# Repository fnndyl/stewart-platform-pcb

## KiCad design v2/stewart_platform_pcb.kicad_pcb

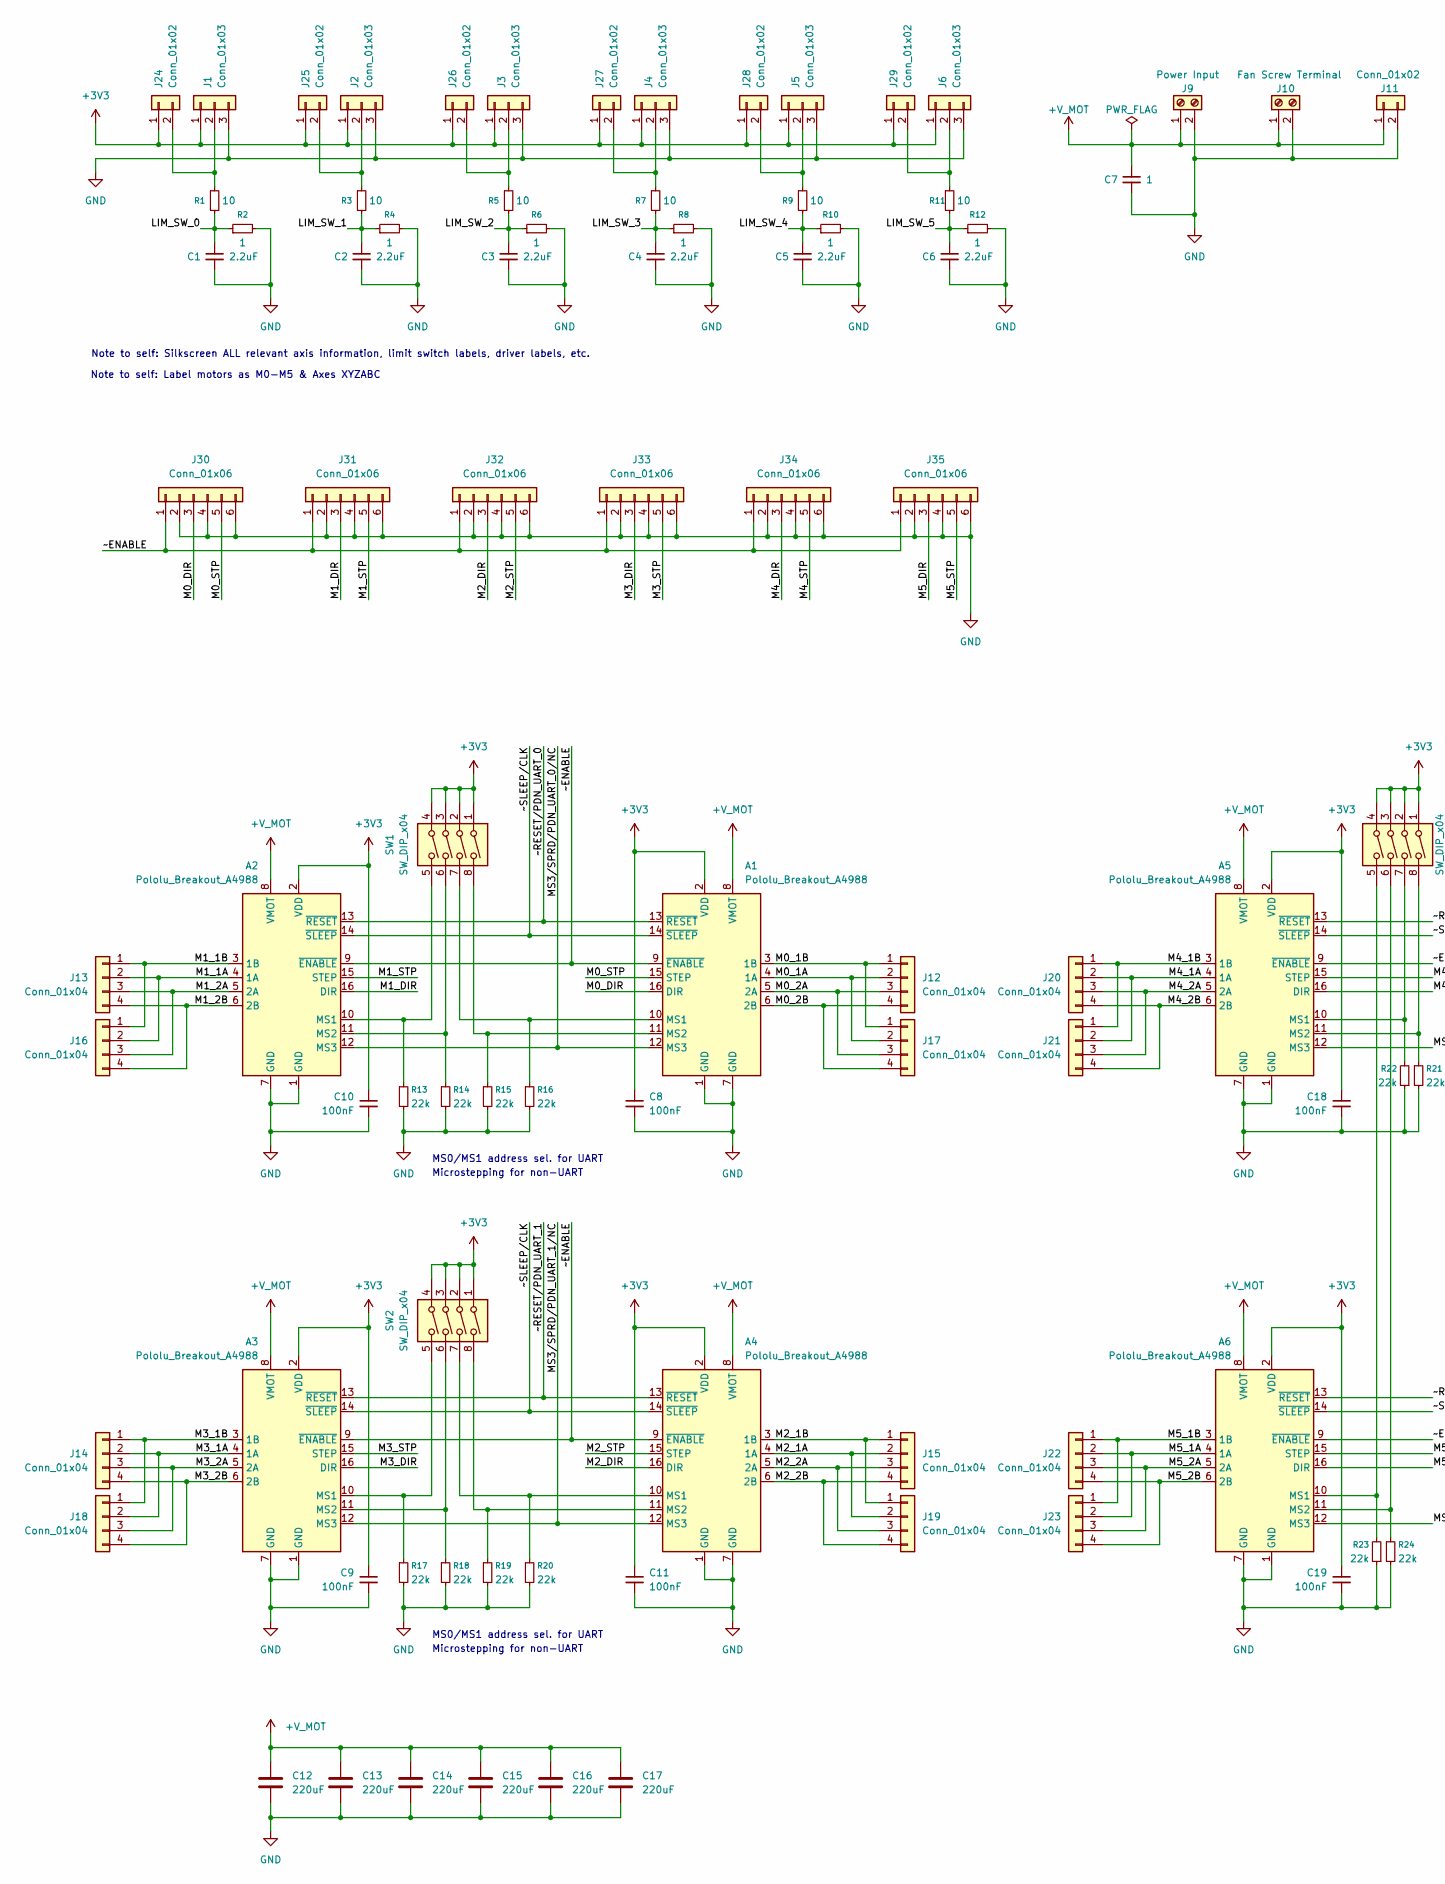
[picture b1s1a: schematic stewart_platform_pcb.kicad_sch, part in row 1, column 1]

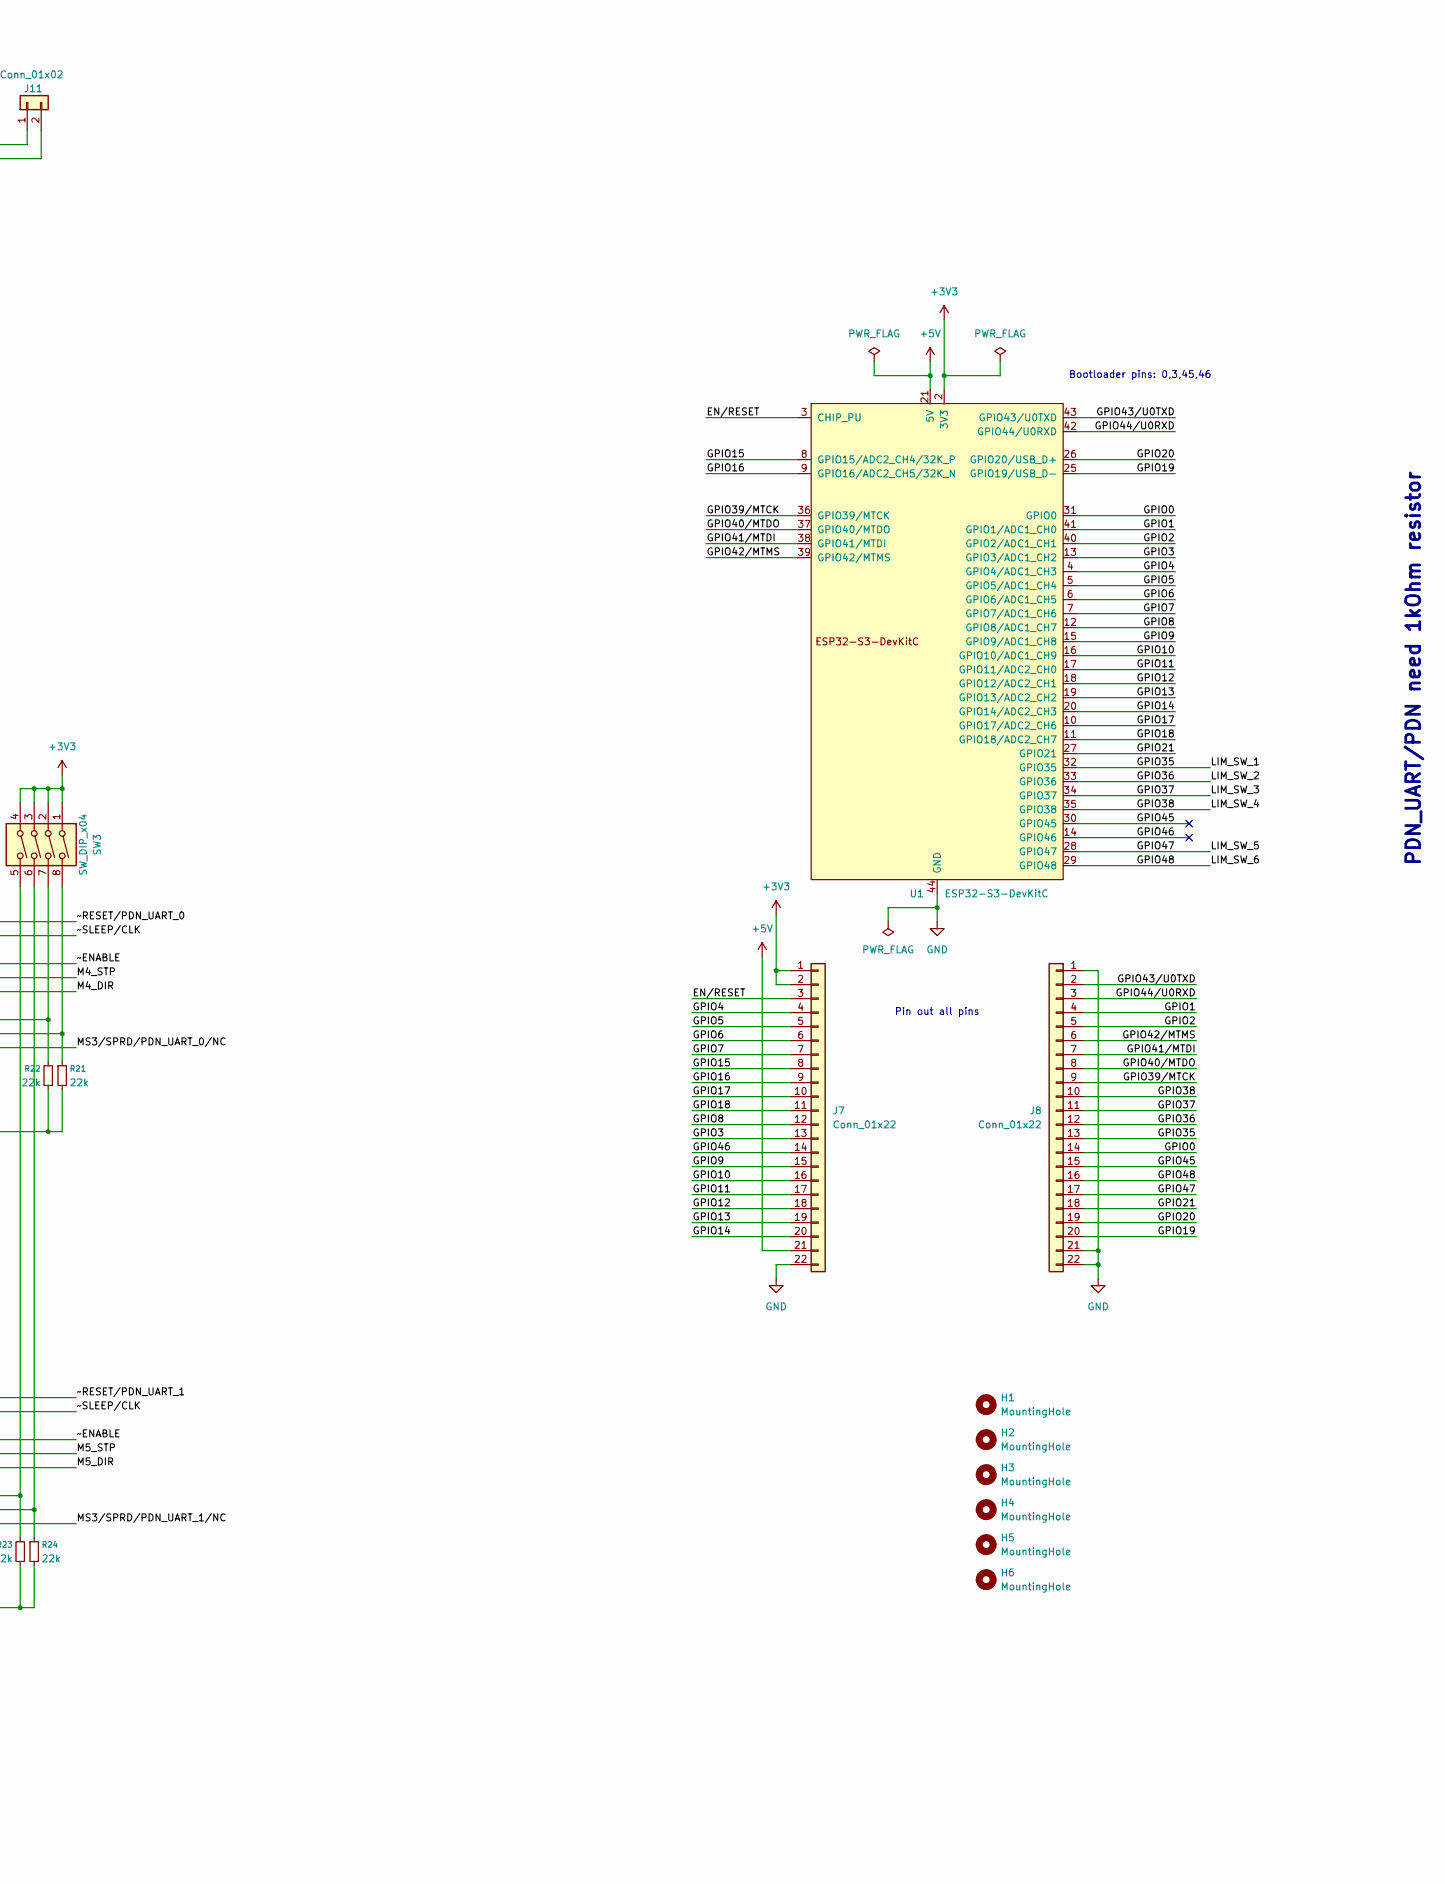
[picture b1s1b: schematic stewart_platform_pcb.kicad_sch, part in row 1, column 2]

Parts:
A1, A2, A3, A4, A5, A6: Pololu_Breakout_A4988; Pololu_Breakout-16_15.2x20.3mm
C1, C2, C3, C4, C5, C6: 2.2uF; C_Radial_D6.3mm_H5.0mm_P2.50mm
C7: 1
C8, C9, C10, C11, C18, C19: 100nF; C_Disc_D4.3mm_W1.9mm_P5.00mm
C12, C13, C14, C15, C16, C17: 220uF; C_Radial_D10.0mm_H12.5mm_P5.00mm
H1, H2, H3, H4, H5, H6: MountingHole; MountingHole_3.2mm_M3
J1, J2, J3, J4, J5, J6: Conn_01x03; JST_XH_B3B-XH-A_1x03_P2.50mm_Vertical
J7, J8: Conn_01x22; PinHeader_1x22_P2.54mm_Vertical
J9: Power Input; TerminalBlock_Phoenix_MKDS-1,5-2_1x02_P5.00mm_Horizontal
J10: Fan Screw Terminal; TerminalBlock_Phoenix_MKDS-1,5-2_1x02_P5.00mm_Horizontal
J11, J24, J25, J26, J27, J28, J29: Conn_01x02; JST_XH_B2B-XH-A_1x02_P2.50mm_Vertical
J12, J13, J14, J15, J16, J17, J18, J19, J20, J21, J22, J23: Conn_01x04; JST_XH_B4B-XH-A_1x04_P2.50mm_Vertical
J30, J31, J32, J33, J34, J35: Conn_01x06; JST_XH_B6B-XH-A_1x06_P2.50mm_Vertical
R1, R3, R5, R7, R9, R11: 10; R_Axial_DIN0207_L6.3mm_D2.5mm_P7.62mm_Horizontal
R2, R4, R6, R8, R10, R12: 1; R_Axial_DIN0207_L6.3mm_D2.5mm_P7.62mm_Horizontal
R13, R14, R15, R16, R17, R18, R19, R20, R21, R22, R23, R24: 22k; R_Axial_DIN0207_L6.3mm_D2.5mm_P7.62mm_Horizontal
SW1, SW2, SW3: SW_DIP_x04; SW_DIP_SPSTx04_Slide_9.78x12.34mm_W7.62mm_P2.54mm
U1: ESP32-S3-DevKitC

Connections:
+3V3: A1.2 (VDD), A2.2 (VDD), A3.2 (VDD), A4.2 (VDD), A5.2 (VDD), A6.2 (VDD), C8.1, C9.1, C10.1, C11.1, C18.1, C19.1, J1.1, J2.1, J3.1, J4.1, J5.1, J6.1, J7.1, J7.2, J24.1, J25.1, J26.1, J27.1, J28.1, J29.1, SW1.1, SW1.2, SW1.3, SW1.4, SW2.1, SW2.2, SW2.3, SW2.4, SW3.1, SW3.2, SW3.3, SW3.4, U1.1 (3V3), U1.2 (3V3)
+5V: J7.21, U1.21 (5V)
+V_MOT: A1.8 (VMOT), A2.8 (VMOT), A3.8 (VMOT), A4.8 (VMOT), A5.8 (VMOT), A6.8 (VMOT), C7.1, C12.1, C13.1, C14.1, C15.1, C16.1, C17.1, J9.1, J10.1, J11.1
/EN/RESET: J7.3, U1.3 (CHIP_PU)
/GPIO0: J8.14, U1.31 (GPIO0)
/GPIO1: J8.4, U1.41 (GPIO1/ADC1_CH0)
/GPIO2: J8.5, U1.40 (GPIO2/ADC1_CH1)
/GPIO3: J7.13, U1.13 (GPIO3/ADC1_CH2)
/GPIO4: J7.4, U1.4 (GPIO4/ADC1_CH3)
/GPIO5: J7.5, U1.5 (GPIO5/ADC1_CH4)
/GPIO6: J7.6, U1.6 (GPIO6/ADC1_CH5)
/GPIO7: J7.7, U1.7 (GPIO7/ADC1_CH6)
/GPIO8: J7.12, U1.12 (GPIO8/ADC1_CH7)
/GPIO9: J7.15, U1.15 (GPIO9/ADC1_CH8)
/GPIO10: J7.16, U1.16 (GPIO10/ADC1_CH9)
/GPIO11: J7.17, U1.17 (GPIO11/ADC2_CH0)
/GPIO12: J7.18, U1.18 (GPIO12/ADC2_CH1)
/GPIO13: J7.19, U1.19 (GPIO13/ADC2_CH2)
/GPIO14: J7.20, U1.20 (GPIO14/ADC2_CH3)
/GPIO15: J7.8, U1.8 (GPIO15/ADC2_CH4/32K_P)
/GPIO16: J7.9, U1.9 (GPIO16/ADC2_CH5/32K_N)
/GPIO17: J7.10, U1.10 (GPIO17/ADC2_CH6)
/GPIO18: J7.11, U1.11 (GPIO18/ADC2_CH7)
/GPIO19: J8.20, U1.25 (GPIO19/USB_D-)
/GPIO20: J8.19, U1.26 (GPIO20/USB_D+)
/GPIO21: J8.18, U1.27 (GPIO21)
/GPIO35: C2.1, J8.13, R3.2, R4.1, U1.32 (GPIO35)
/GPIO36: C3.1, J8.12, R5.2, R6.1, U1.33 (GPIO36)
/GPIO37: C4.1, J8.11, R7.2, R8.1, U1.34 (GPIO37)
/GPIO38: C5.1, J8.10, R9.2, R10.1, U1.35 (GPIO38)
/GPIO39/MTCK: J8.9, U1.36 (GPIO39/MTCK)
/GPIO40/MTDO: J8.8, U1.37 (GPIO40/MTDO)
/GPIO41/MTDI: J8.7, U1.38 (GPIO41/MTDI)
/GPIO42/MTMS: J8.6, U1.39 (GPIO42/MTMS)
/GPIO43/U0TXD: J8.2, U1.43 (GPIO43/U0TXD)
/GPIO44/U0RXD: J8.3, U1.42 (GPIO44/U0RXD)
/GPIO45: J8.15, U1.30 (GPIO45)
/GPIO46: J7.14, U1.14 (GPIO46)
/GPIO47: C6.1, J8.17, R11.2, R12.1, U1.28 (GPIO47)
/GPIO48: J8.16, U1.29 (GPIO48)
/LIM_SW_0: C1.1, R1.2, R2.1
/M0_1A: A1.4 (1A), J12.2, J17.2
/M0_1B: A1.3 (1B), J12.1, J17.1
/M0_2A: A1.5 (2A), J12.3, J17.3
/M0_2B: A1.6 (2B), J12.4, J17.4
/M0_DIR: A1.16 (DIR), J30.3
/M0_STP: A1.15 (STEP), J30.5
/M1_1A: A2.4 (1A), J13.2, J16.2
/M1_1B: A2.3 (1B), J13.1, J16.1
/M1_2A: A2.5 (2A), J13.3, J16.3
/M1_2B: A2.6 (2B), J13.4, J16.4
/M1_DIR: A2.16 (DIR), J31.3
/M1_STP: A2.15 (STEP), J31.5
/M2_1A: A4.4 (1A), J15.2, J19.2
/M2_1B: A4.3 (1B), J15.1, J19.1
/M2_2A: A4.5 (2A), J15.3, J19.3
/M2_2B: A4.6 (2B), J15.4, J19.4
/M2_DIR: A4.16 (DIR), J32.3
/M2_STP: A4.15 (STEP), J32.5
/M3_1A: A3.4 (1A), J14.2, J18.2
/M3_1B: A3.3 (1B), J14.1, J18.1
/M3_2A: A3.5 (2A), J14.3, J18.3
/M3_2B: A3.6 (2B), J14.4, J18.4
/M3_DIR: A3.16 (DIR), J33.3
/M3_STP: A3.15 (STEP), J33.5
/M4_1A: A5.4 (1A), J20.2, J21.2
/M4_1B: A5.3 (1B), J20.1, J21.1
/M4_2A: A5.5 (2A), J20.3, J21.3
/M4_2B: A5.6 (2B), J20.4, J21.4
/M4_DIR: A5.16 (DIR), J34.3
/M4_STP: A5.15 (STEP), J34.5
/M5_1A: A6.4 (1A), J22.2, J23.2
/M5_1B: A6.3 (1B), J22.1, J23.1
/M5_2A: A6.5 (2A), J22.3, J23.3
/M5_2B: A6.6 (2B), J22.4, J23.4
/M5_DIR: A6.16 (DIR), J35.3
/M5_STP: A6.15 (STEP), J35.5
/MS3/SPRD/PDN_UART_0/NC: A1.12 (MS3), A2.12 (MS3), A5.12 (MS3)
/MS3/SPRD/PDN_UART_1/NC: A3.12 (MS3), A4.12 (MS3), A6.12 (MS3)
/~ENABLE: A1.9 (~ENABLE), A2.9 (~ENABLE), A3.9 (~ENABLE), A4.9 (~ENABLE), A5.9 (~ENABLE), A6.9 (~ENABLE), J30.1, J31.1, J32.1, J33.1, J34.1, J35.1
/~RESET/PDN_UART_0: A1.13 (~RESET), A2.13 (~RESET), A5.13 (~RESET)
/~RESET/PDN_UART_1: A3.13 (~RESET), A4.13 (~RESET), A6.13 (~RESET)
/~SLEEP/CLK: A1.14 (~SLEEP), A2.14 (~SLEEP), A3.14 (~SLEEP), A4.14 (~SLEEP), A5.14 (~SLEEP), A6.14 (~SLEEP)
GND: A1.1 (GND), A1.7 (GND), A2.1 (GND), A2.7 (GND), A3.1 (GND), A3.7 (GND), A4.1 (GND), A4.7 (GND), A5.1 (GND), A5.7 (GND), A6.1 (GND), A6.7 (GND), C1.2, C2.2, C3.2, C4.2, C5.2, C6.2, C7.2, C8.2, C9.2, C10.2, C11.2, C12.2, C13.2, C14.2, C15.2, C16.2, C17.2, C18.2, C19.2, J1.3, J2.3, J3.3, J4.3, J5.3, J6.3, J7.22, J8.1, J8.21, J8.22, J9.2, J10.2, J11.2, J30.2, J30.4, J30.6, J31.2, J31.4, J31.6, J32.2, J32.4, J32.6, J33.2, J33.4, J33.6, J34.2, J34.4, J34.6, J35.2, J35.4, J35.6, R2.2, R4.2, R6.2, R8.2, R10.2, R12.2, R13.2, R14.2, R15.2, R16.2, R17.2, R18.2, R19.2, R20.2, R21.2, R22.1, R23.1, R24.2, U1.22 (GND), U1.23 (GND), U1.24 (GND), U1.44 (GND)
unnamed: A1.10 (MS1), R16.1, SW1.7
unnamed: A1.11 (MS2), R15.1, SW1.8
unnamed: A2.10 (MS1), R13.1, SW1.5
unnamed: A2.11 (MS2), R14.1, SW1.6
unnamed: A3.10 (MS1), R17.1, SW2.5
unnamed: A3.11 (MS2), R18.1, SW2.6
unnamed: A4.10 (MS1), R20.1, SW2.7
unnamed: A4.11 (MS2), R19.1, SW2.8
unnamed: A5.10 (MS1), R22.2, SW3.7
unnamed: A5.11 (MS2), R21.1, SW3.8
unnamed: A6.10 (MS1), R23.2, SW3.5
unnamed: A6.11 (MS2), R24.1, SW3.6
unnamed: J1.2, J24.2, R1.1
unnamed: J2.2, J25.2, R3.1
unnamed: J3.2, J26.2, R5.1
unnamed: J4.2, J27.2, R7.1
unnamed: J5.2, J28.2, R9.1
unnamed: J6.2, J29.2, R11.1

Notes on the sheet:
MS0/MS1 address sel. for UART
PDN_UART/PDN need 1kOhm resistor
Microstepping for non-UART
Pin out all pins
Note to self: Label motors as M0-M5 & Axes XYZABC
Note to self: Silkscreen ALL relevant axis information, limit switch labels, driver labels, etc.
Bootloader pins: 0,3,45,46

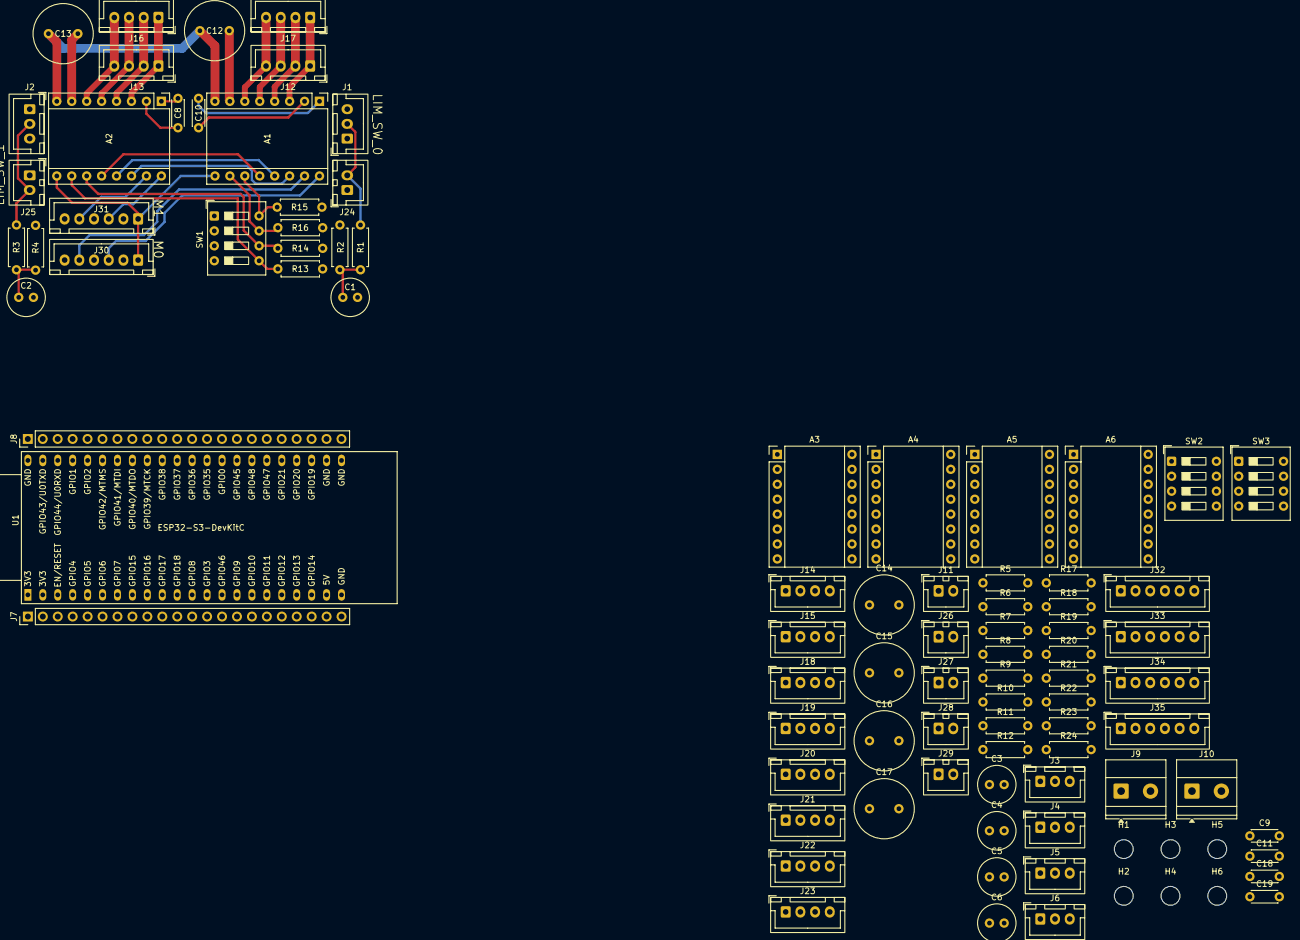
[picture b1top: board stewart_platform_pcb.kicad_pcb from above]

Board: 4 copper layers, 93 parts (0 on the bottom side), 102 nets.

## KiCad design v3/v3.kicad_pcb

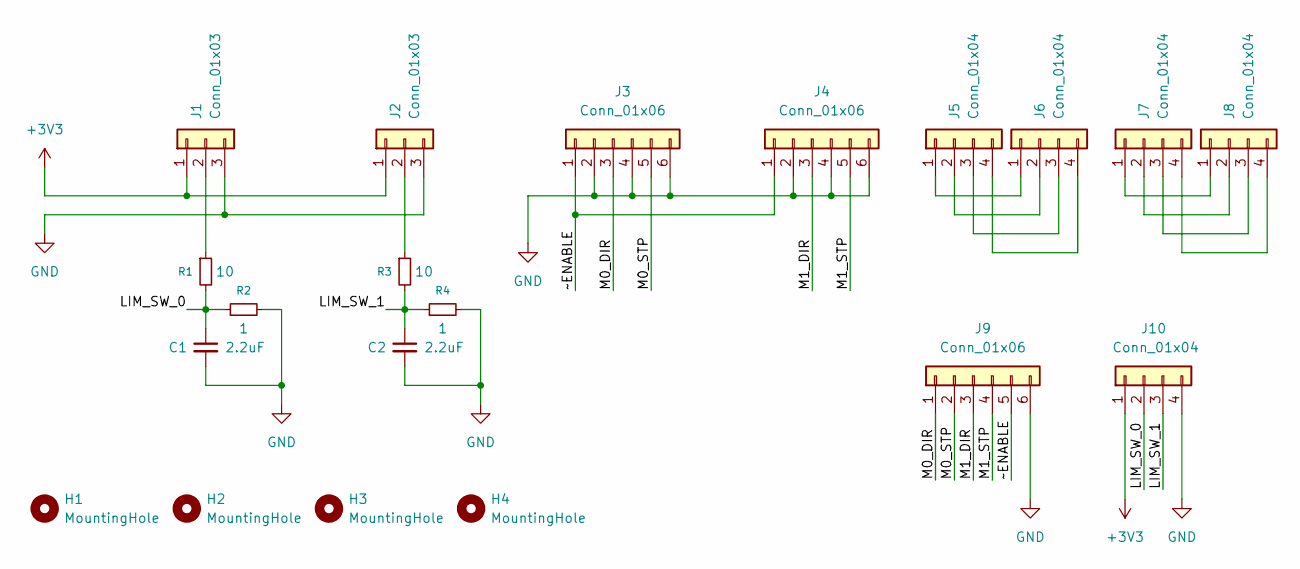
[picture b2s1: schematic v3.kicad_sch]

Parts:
C1, C2: 2.2uF; C_Radial_D6.3mm_H5.0mm_P2.50mm
H1, H2, H3, H4: MountingHole; MountingHole_3.2mm_M3
J1, J2: Conn_01x03; JST_XH_B3B-XH-A_1x03_P2.50mm_Vertical
J3, J4, J9: Conn_01x06; JST_XH_B6B-XH-A_1x06_P2.50mm_Vertical
J5, J6, J7, J8, J10: Conn_01x04; JST_XH_B4B-XH-A_1x04_P2.50mm_Vertical
R1, R3: 10; R_Axial_DIN0207_L6.3mm_D2.5mm_P7.62mm_Horizontal
R2, R4: 1; R_Axial_DIN0207_L6.3mm_D2.5mm_P7.62mm_Horizontal

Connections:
+3V3: J1.1, J2.1, J10.1
/LIM_SW_0: C1.1, J10.2, R1.2, R2.1
/LIM_SW_1: C2.1, J10.3, R3.2, R4.1
/M0_DIR: J3.3, J9.1
/M0_STP: J3.5, J9.2
/M1_DIR: J4.3, J9.3
/M1_STP: J4.5, J9.4
/~ENABLE: J3.1, J4.1, J9.5
GND: C1.2, C2.2, J1.3, J2.3, J3.2, J3.4, J3.6, J4.2, J4.4, J4.6, J9.6, J10.4, R2.2, R4.2
unnamed: J1.2, R1.1
unnamed: J2.2, R3.1
unnamed: J5.1, J6.1
unnamed: J5.2, J6.2
unnamed: J5.3, J6.3
unnamed: J5.4, J6.4
unnamed: J7.1, J8.1
unnamed: J7.2, J8.2
unnamed: J7.3, J8.3
unnamed: J7.4, J8.4

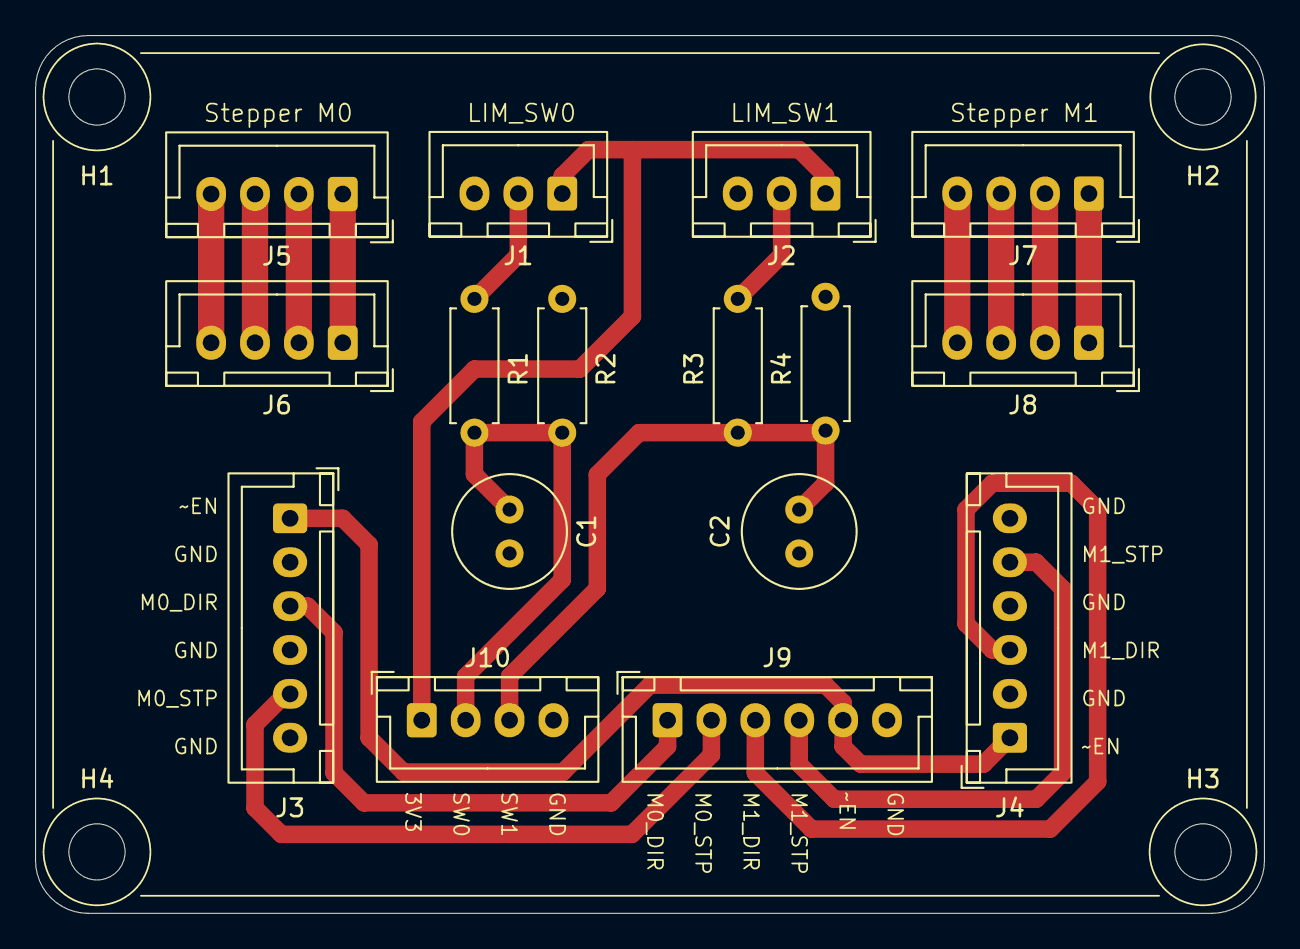
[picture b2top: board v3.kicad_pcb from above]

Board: 2 copper layers, 70.0 x 50.0 mm, 20 parts (0 on the bottom side), 19 nets.

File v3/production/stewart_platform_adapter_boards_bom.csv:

Designator,Footprint,Quantity,Value,LCSC Part #
"C1, C2",C_Radial_D6.3mm_H5.0mm_P2.50mm,2,2.2uF,
"J1, J2",JST_XH_B3B-XH-A_1x03_P2.50mm_Vertical,2,Conn_01x03,
"J10, J5, J6, J7, J8",JST_XH_B4B-XH-A_1x04_P2.50mm_Vertical,5,Conn_01x04,
"J3, J4, J9",JST_XH_B6B-XH-A_1x06_P2.50mm_Vertical,3,Conn_01x06,
"R1, R3",R_Axial_DIN0207_L6.3mm_D2.5mm_P7.62mm_Horizontal,2,10,
"R2, R4",R_Axial_DIN0207_L6.3mm_D2.5mm_P7.62mm_Horizontal,2,1,

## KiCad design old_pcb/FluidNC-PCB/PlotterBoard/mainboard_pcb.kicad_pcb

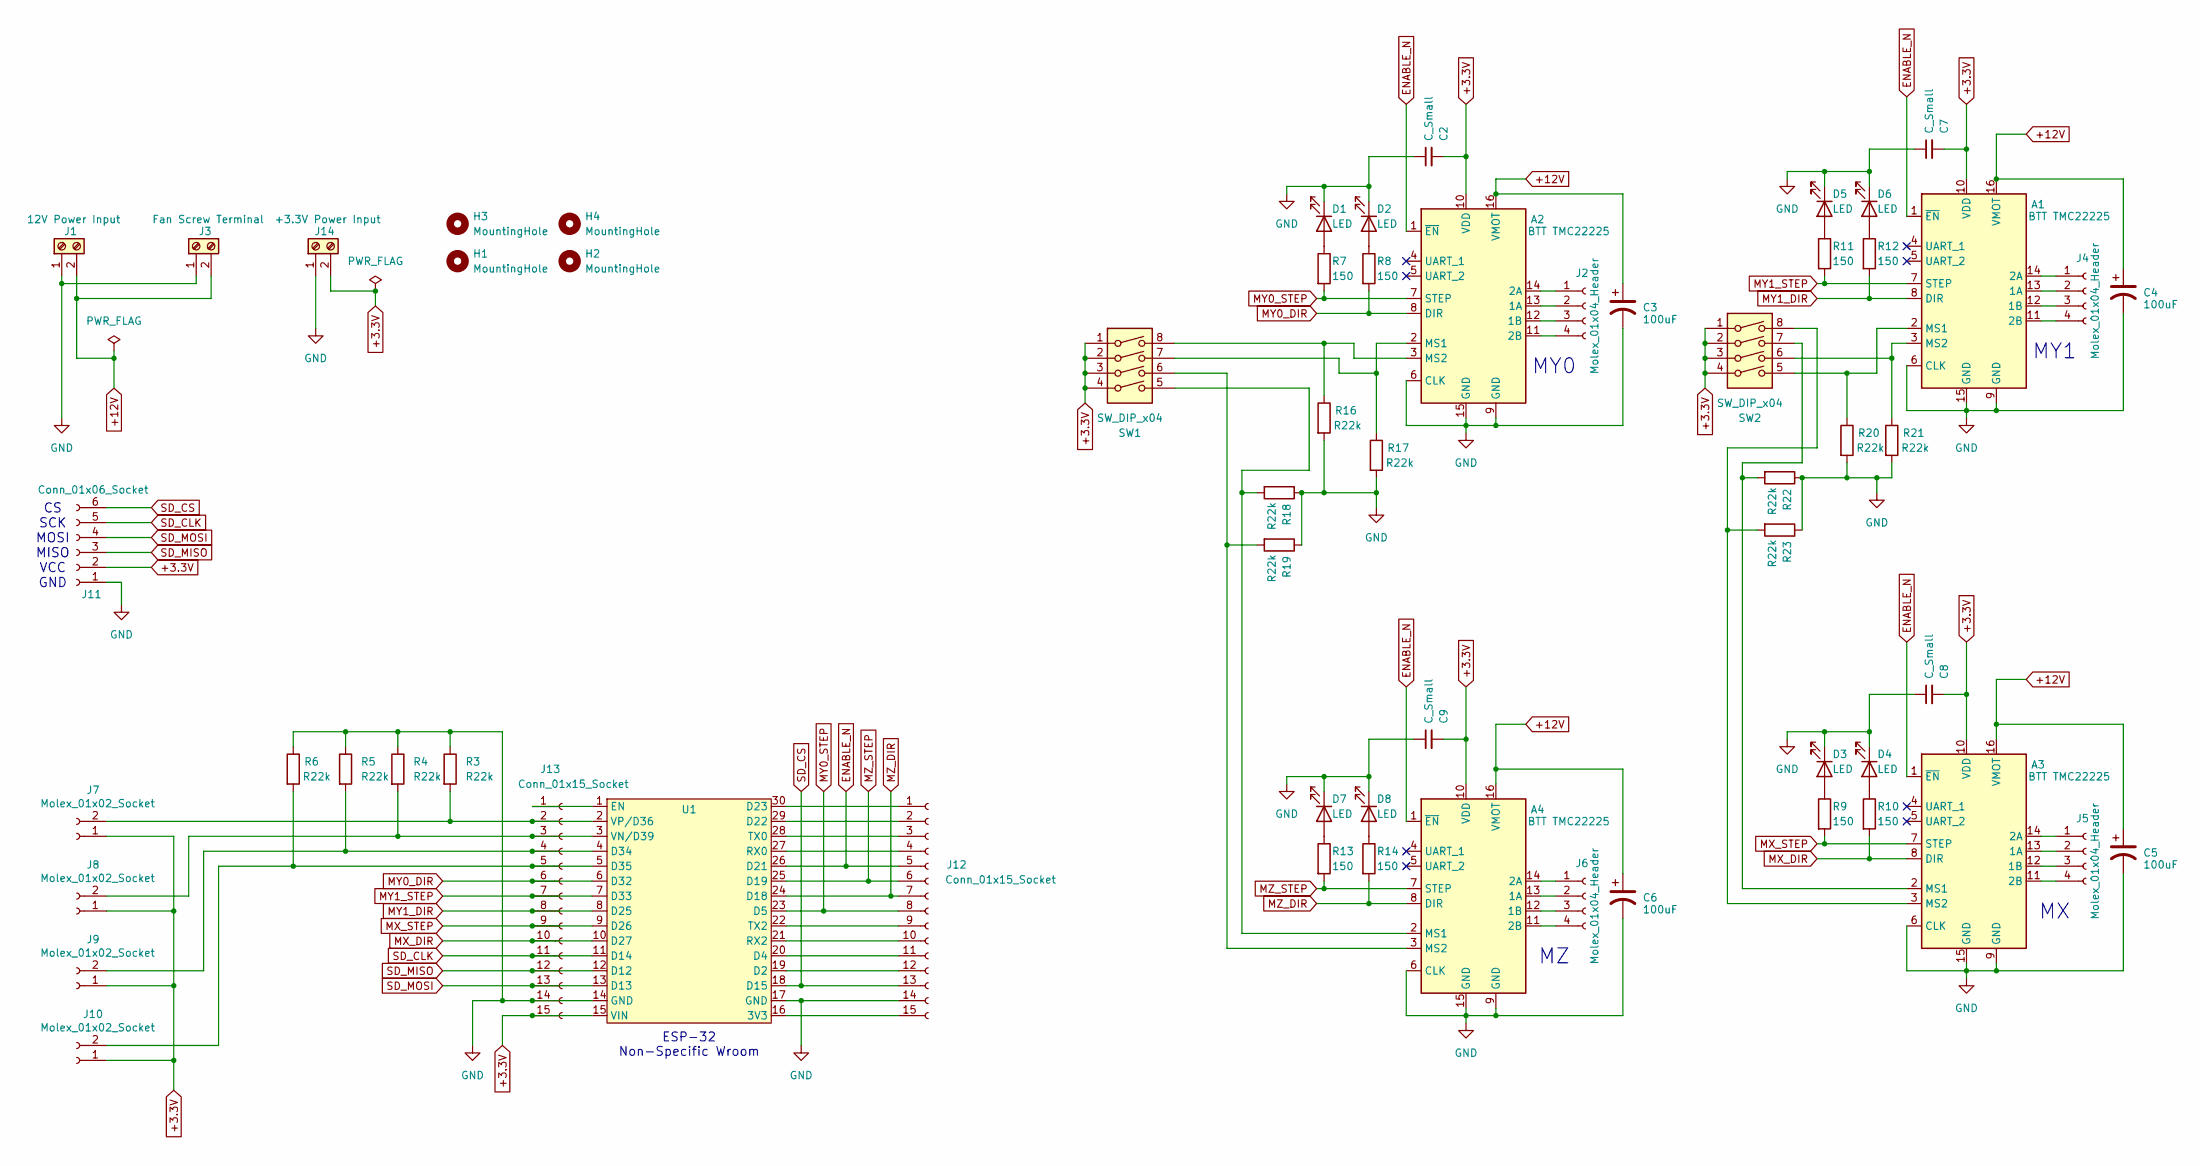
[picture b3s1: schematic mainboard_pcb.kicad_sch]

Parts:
A1, A2, A3, A4: BTT TMC22225; BTT TMC 2225 Footprint
C2, C7, C8, C9: C_Small; C_Disc_D4.3mm_W1.9mm_P5.00mm
C3, C4, C5, C6: 100uF; C_Radial_D8.0mm_H11.5mm_P3.50mm
D1, D2, D3, D4, D5, D6, D7, D8: LED; LED_D3.0mm
H1, H2, H3, H4: MountingHole; MountingHole_3.2mm_M3
J1: 12V Power Input; TerminalBlock_Phoenix_MKDS-1,5-2_1x02_P5.00mm_Horizontal
J2, J4, J5, J6: Molex_01x04_Header; Molex_KK-254_AE-6410-04A_1x04_P2.54mm_Vertical
J3: Fan Screw Terminal; TerminalBlock_Phoenix_MKDS-1,5-2_1x02_P5.00mm_Horizontal
J7, J8, J9, J10: Molex_01x02_Socket; Molex_KK-254_AE-6410-02A_1x02_P2.54mm_Vertical
J11: Conn_01x06_Socket; PinSocket_1x06_P2.54mm_Vertical
J12, J13: Conn_01x15_Socket; PinSocket_1x15_P2.54mm_Vertical
J14: +3.3V Power Input; TerminalBlock_Phoenix_MKDS-1,5-2_1x02_P5.00mm_Horizontal
R3, R4, R5, R6, R16, R17, R18, R19, R20, R21, R22, R23: R22k; R_Axial_DIN0204_L3.6mm_D1.6mm_P5.08mm_Horizontal
R7, R8, R9, R10, R11, R12, R13, R14: 150; R_Axial_DIN0204_L3.6mm_D1.6mm_P5.08mm_Horizontal
SW1, SW2: SW_DIP_x04; SW_DIP_SPSTx04_Slide_9.78x12.34mm_W7.62mm_P2.54mm
U1: esp32-mystery-footprint

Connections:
+3.3V: A1.10 (VDD), A2.10 (VDD), A3.10 (VDD), A4.10 (VDD), C2.2, C7.2, C8.2, C9.2, J7.1, J8.1, J9.1, J10.1, J11.2, J13.15, J14.2, SW1.1, SW1.2, SW1.3, SW1.4, SW2.1, SW2.2, SW2.3, SW2.4, U1.15 (VIN)
+12V: A1.16 (VMOT), A2.16 (VMOT), A3.16 (VMOT), A4.16 (VMOT), C3.1, C4.1, C5.1, C6.1, J1.2, J3.2
ENABLE_N: A1.1 (~EN), A2.1 (~EN), A3.1 (~EN), A4.1 (~EN), J12.5, U1.26 (D21)
GND: A1.6 (CLK), A1.9 (GND), A1.15 (GND), A2.6 (CLK), A2.9 (GND), A2.15 (GND), A3.6 (CLK), A3.9 (GND), A3.15 (GND), A4.6 (CLK), A4.9 (GND), A4.15 (GND), C2.1, C3.2, C4.2, C5.2, C6.2, C7.1, C8.1, C9.1, D1.1 (K), D2.1 (K), D3.1 (K), D4.1 (K), D5.1 (K), D6.1 (K), D7.1 (K), D8.1 (K), J1.1, J3.1, J11.1, J12.14, J13.14, J14.1, R3.1, R4.1, R5.1, R6.1, R16.2, R17.2, R18.1, R19.1, R20.2, R21.2, R22.1, R23.1, U1.14 (GND), U1.17 (GND)
MX_DIR: A3.8 (DIR), J13.10, R10.2, U1.10 (D27)
MX_STEP: A3.7 (STEP), J13.9, R9.2, U1.9 (D26)
MY0_DIR: A2.8 (DIR), J13.6, R8.2, U1.6 (D32)
MY0_STEP: A2.7 (STEP), J12.8, R7.2, U1.23 (D5)
MY1_DIR: A1.8 (DIR), J13.8, R12.2, U1.8 (D25)
MY1_STEP: A1.7 (STEP), J13.7, R11.2, U1.7 (D33)
MZ_DIR: A4.8 (DIR), J12.7, R14.2, U1.24 (D18)
MZ_STEP: A4.7 (STEP), J12.6, R13.2, U1.25 (D19)
unnamed: A1.13 (1A), J4.2
unnamed: A1.12 (1B), J4.3
unnamed: A1.14 (2A), J4.1
unnamed: A1.11 (2B), J4.4
unnamed: A1.2 (MS1), R20.1, SW2.5
unnamed: A1.3 (MS2), R21.1, SW2.6
unnamed: A2.13 (1A), J2.2
unnamed: A2.12 (1B), J2.3
unnamed: A2.14 (2A), J2.1
unnamed: A2.11 (2B), J2.4
unnamed: A2.2 (MS1), R17.1, SW1.7
unnamed: A2.3 (MS2), R16.1, SW1.8
unnamed: A3.13 (1A), J5.2
unnamed: A3.12 (1B), J5.3
unnamed: A3.14 (2A), J5.1
unnamed: A3.11 (2B), J5.4
unnamed: A3.2 (MS1), R22.2, SW2.7
unnamed: A3.3 (MS2), R23.2, SW2.8
unnamed: A4.13 (1A), J6.2
unnamed: A4.12 (1B), J6.3
unnamed: A4.14 (2A), J6.1
unnamed: A4.11 (2B), J6.4
unnamed: A4.2 (MS1), R18.2, SW1.5
unnamed: A4.3 (MS2), R19.2, SW1.6
unnamed: D1.2 (A), R7.1
unnamed: D2.2 (A), R8.1
unnamed: D3.2 (A), R9.1
unnamed: D4.2 (A), R10.1
unnamed: D5.2 (A), R11.1
unnamed: D6.2 (A), R12.1
unnamed: D7.2 (A), R13.1
unnamed: D8.2 (A), R14.1
unnamed: J10.2, J13.5, R6.2, U1.5 (D35)
unnamed: J12.1, U1.30 (D23)
unnamed: J12.2, U1.29 (D22)
unnamed: J12.3, U1.28 (TX0)
unnamed: J12.4, U1.27 (RX0)
unnamed: J12.9, U1.22 (TX2)
unnamed: J12.10, U1.21 (RX2)
unnamed: J12.11, U1.20 (D4)
unnamed: J12.12, U1.19 (D2)
unnamed: J12.15, U1.16 (3V3)
unnamed: J13.1, U1.1 (EN)
unnamed: J7.2, J13.2, R3.2, U1.2 (VP/D36)
unnamed: J8.2, J13.3, R4.2, U1.3 (VN/D39)
unnamed: J9.2, J13.4, R5.2, U1.4 (D34)
SD_CLK: J11.5, J13.11, U1.11 (D14)
SD_CS: J11.6, J12.13, U1.18 (D15)
SD_MISO: J11.3, J13.12, U1.12 (D12)
SD_MOSI: J11.4, J13.13, U1.13 (D13)

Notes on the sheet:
CS SCK MOSI MISO VCC GND
ESP-32 Non-Specific Wroom
MY0
MY1

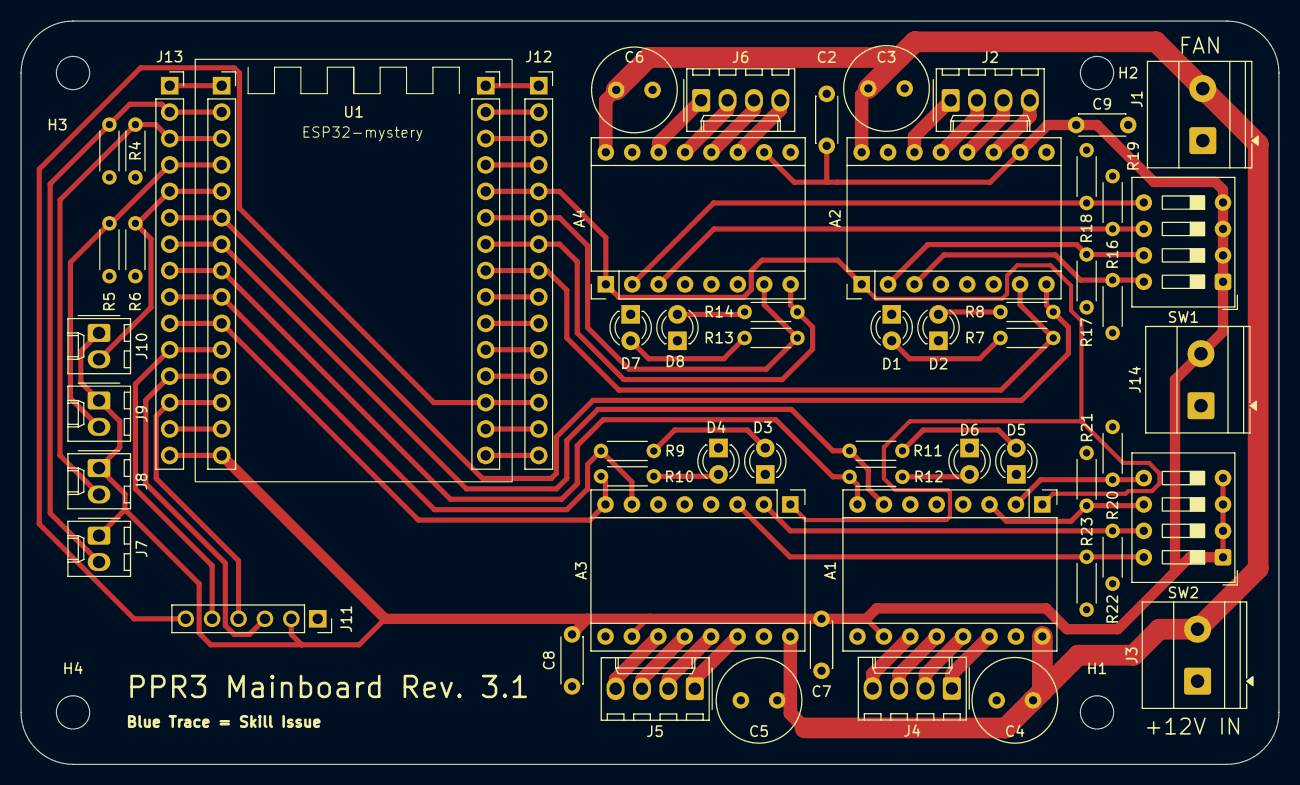
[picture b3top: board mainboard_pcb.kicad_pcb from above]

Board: 2 copper layers, 121.0 x 71.5 mm, 61 parts (0 on the bottom side), 62 nets.

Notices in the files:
v1/FluidNC-PCB/FluidNC-PCB.kicad_pcb:
License: CERN-OHL-P
